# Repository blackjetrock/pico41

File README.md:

This project has been superseded by Tulip
=========================================

It is recommeded that the Tulip project is used instead of this one. It can be found here:

https://github.com/mjakuipers/TULIP-DevBoard

It has more features, by far. The only feature that it doesn't have is the key pressing, but it does have many more ways to enter programs...

Pico41
======

This is a PCB that can be attached to an HP41C (using wires soldered to the processor PCB of the HP41C) that allows:

* The HP41C bus to be examined and traced
* Data to be placed on the bus
* Keys on the keyboard to be pressed
* viewing of the display on an OLED display on the PCB

You can see what is happening on the bus just like a logic analyser. The tracing (and other interaction) is through the USB of the Pico.
You can emulate modules by putting appropriate words on the bus. Currently I have emulated a MATH module. Bank switched modules aren't supported, nor are RAM modules, but that is just a matter of code that I haven't done yet.
You can press keys on the keyboard, so can enter programs by pressing the appropriate keys. I have a script that converts program in text form and embeds the keypresses into the Pico program such that they can be played back in PRGM mode. Once entered like this the program can be SST'd automatically and checked against a listing that is also embedded in the Pio program.

RP Pico on HP41C bus, showing an emulated MATH module where one word has been altered:

To Do
=====

It should be possible to emulate the display controller and use this Pico setup as a replacement for the display controller. For example a broken display controller should be replaceable by this program.
RAM should also be emulatable with more code.
Module code could be changed over USB rather than being embedded in the Pico code as it is now.

More Information
================

* https://youtu.be/KFQwrbWywjY
* https://youtu.be/kRxo2ekzvyg

This is a work in progress
==========================

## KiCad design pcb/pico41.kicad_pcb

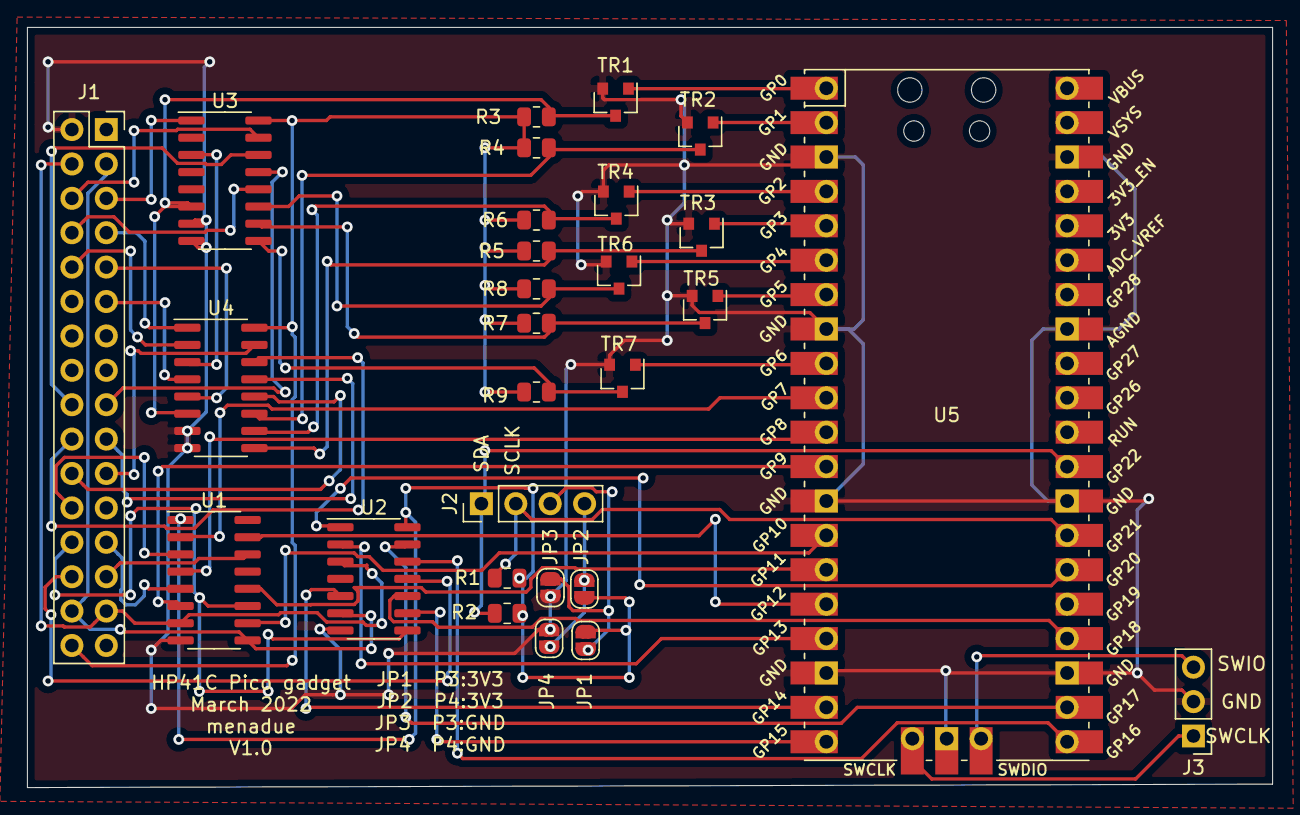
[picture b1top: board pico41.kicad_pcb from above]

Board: 2 copper layers, 91.9 x 56.1 mm, 28 parts (0 on the bottom side), 57 nets.

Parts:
J1: Conn_02x16_Counter_Clockwise; PinSocket_2x16_P2.54mm_Vertical
J2: Conn_01x04_Female; PinHeader_1x04_P2.54mm_Vertical
J3: Conn_01x03_Female; PinHeader_1x03_P2.54mm_Vertical
JP1, JP2, JP3, JP4: Jumper_NO_Small; SolderJumper-2_P1.3mm_Open_RoundedPad1.0x1.5mm
R1, R2: 4k7; R_0805_2012Metric
R3, R4, R5, R6, R7, R8, R9: 10k; R_0805_2012Metric
TR1: Si2302; SOT-23
TR2, TR3, TR4, TR5, TR6, TR7: si2302; SOT-23
U1: 4050; SOIC-16_3.9x9.9mm_P1.27mm
U2: 74LS125; SOIC-14_3.9x8.7mm_P1.27mm
U3, U4: 4051; SOIC-16_3.9x9.9mm_P1.27mm
U5: Pico; RPi_Pico_SMD_TH

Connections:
3V3: JP1.1, JP2.1, R1.1, R2.1, U1.1, U2.14
DATA: J1.4, J1.29, U1.7, U2.3
FI: J1.28, U2.11
GND: J1.2, J3.2, JP3.1, JP4.1, TR1.2, TR2.2, TR3.2, TR4.2, TR5.2, TR6.2, TR7.2, U1.8, U2.7, U3.7, U3.8, U4.7, U4.8, U5.3, U5.8, U5.13, U5.18, U5.23, U5.28, U5.33, U5.38, U5.42
I2C_SCL: J2.2, R1.2, U5.27
I2C_SDA: J2.1, R2.2, U5.29
ISA: J1.3, J1.30, U1.9, U2.6
KB_INH: R3.2, TR1.3, U3.6, U4.6
KC0: J1.17, U3.13
KC1: J1.18, U3.14
KC2: J1.6, U3.15
KC3: J1.8, U3.12
KC4: J1.5, U3.1
KCA: R8.2, TR6.3, U3.11
KCB: R7.2, TR5.3, U3.10
KCC: R9.2, TR7.3, U3.9
KR0: J1.19, U4.13
KR1: J1.20, U4.14
KR2: J1.21, U4.15
KR3: J1.22, U4.12
KR4: J1.7, U4.1
KR5: J1.9, U4.5
KR6: J1.10, U4.2
KR7: J1.11, U4.4
KRA: R4.2, TR2.3, U4.11
KRB: R6.2, TR4.3, U4.10
KRC: R5.2, TR3.3, U4.9
unnamed: J2.3, JP1.2, JP3.2
unnamed: J2.4, JP2.2, JP4.2
unnamed: U3.3, U4.3
PHI1: J1.24, U1.3
PHI2: J1.25, U1.5
PWO: J1.27, U1.14
P_DATA: U1.6, U5.12
P_DATA_DRV: U2.2, U5.17
P_DATA_OE: U2.1, U5.26
P_FI_DRV: U2.12, U5.21
P_FI_OE: U2.13, U5.22
P_ISA: U1.10, U5.14
P_ISA_DRV: U2.5, U5.19
P_KB_INH: TR1.1, U5.1
P_KCA: TR6.1, U5.6
P_KCB: TR5.1, U5.7
P_KCC: TR7.1, U5.9
P_KRA: TR2.1, U5.2
P_KRB: TR4.1, U5.4
P_KRC: TR3.1, U5.5
P_PHI1: U1.2, U5.10
P_PHI2: U1.4, U5.11
P_PWO: U1.15, U5.16
P_SYNC: U1.12, U5.15
P_SYNC_DRV: U2.9, U5.20
P_SYNC_OE: U2.10, U5.24
SWCLK: J3.1, U5.41
SWIO: J3.3, U5.43
SYNC: J1.26, U1.11, U2.8
VCC: J1.32, R3.1, R4.1, R5.1, R6.1, R7.1, R8.1, R9.1, U3.16, U4.16

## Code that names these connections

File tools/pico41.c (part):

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// GPIO Pins
//

const uint P_KB_INH            = 0;
const uint P_KRA               = 1;
const uint P_KRB               = 2;
const uint P_KRC               = 3;

const uint P_KCA               = 4;
const uint P_KCB               = 5;
const uint P_KCC               = 6;

const uint P_CLK1              = 7;
const uint P_CLK2              = 8;

const uint P_DATA              = 9;
const uint P_ISA               = 10;
const uint P_SYNC              = 11;
const uint P_PWO               = 12;
const uint P_DATA_DRV          = 13;
const uint P_ISA_DRV           = 14;
const uint P_SYNC_DRV          = 15;
const uint P_FI_DRV            = 16;
const uint P_FI_OE             = 17;
const uint P_SYNC_OE           = 18;
const uint P_ISA_OE            = 19;
const uint P_DATA_OE           = 20;

// For the OLED display
const uint SDA_PIN             = 22;
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  while(1)
    {
      // All switches off
      gpio_put(P_KB_INH, 0);
      sleep_us(1);
      gpio_put(P_KB_INH, 1);
      sleep_us(1);
    }
#endif
        gpio_put(P_KB_INH, 1);
}


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
void kb_init()
{
  gpio_init(P_KB_INH);
  gpio_init(P_KRA);
  gpio_init(P_KRB);
  gpio_init(P_KRC);
  gpio_init(P_KCA);
  gpio_init(P_KCB);
  gpio_init(P_KCC);

#if 1
  gpio_set_dir(P_KB_INH, GPIO_OUT);
  gpio_set_dir(P_KRA, GPIO_OUT);
  gpio_set_dir(P_KRB, GPIO_OUT);
  gpio_set_dir(P_KRC, GPIO_OUT);
  gpio_set_dir(P_KCA, GPIO_OUT);
  gpio_set_dir(P_KCB, GPIO_OUT);
  gpio_set_dir(P_KCC, GPIO_OUT);
#endif
  
  kb_all_off();
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
void drv_init(void)
{
  const uint P_FI_OE             = 17;
const uint P_SYNC_OE           = 18;
const uint P_ISA_OE            = 19;
const uint P_DATA_OE           = 20;

  gpio_init(P_FI_OE);
  gpio_init(P_SYNC_OE);
  gpio_init(P_ISA_OE);
  gpio_init(P_DATA_OE);

  gpio_set_dir(P_FI_OE, GPIO_OUT);
  gpio_set_dir(P_SYNC_OE, GPIO_OUT);
  gpio_set_dir(P_ISA_OE, GPIO_OUT);
  gpio_set_dir(P_DATA_OE, GPIO_OUT);

  gpio_put(P_FI_OE, 1);
  gpio_put(P_SYNC_OE, 1);
  gpio_put(P_ISA_OE, 1);
  gpio_put(P_DATA_OE, 1);

  gpio_init(P_ISA_DRV);
  gpio_set_dir(P_ISA_DRV, GPIO_OUT);
  gpio_put(P_ISA_DRV, 0);
}

////////////////////////////////////////////////////////////////////////////////
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  gpio_set_dir(P_CLK1, GPIO_IN);
  gpio_init(P_CLK2);
  gpio_set_dir(P_CLK2, GPIO_IN);
  gpio_init(P_SYNC);
  gpio_set_dir(P_SYNC, GPIO_IN);
  gpio_init(P_ISA);
  gpio_set_dir(P_ISA, GPIO_IN);
  gpio_init(P_DATA);
  gpio_set_dir(P_DATA, GPIO_IN);
  
}

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  
  // Wait for falling edge of sync, that is the start of a cycle
  
  last_sync = gpio_get(P_SYNC);
  
  while(1)
    {
      sync = gpio_get(P_SYNC);
      if( (last_sync==1) && (sync==0) )
	{
	  // Start of cycle
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    {
      fclk1[i] = gpio_get(P_CLK1);
      fclk2[i] = gpio_get(P_CLK2);
      fsync[i] = gpio_get(P_SYNC);
      fisa[i] =  gpio_get(P_ISA);
      fdata[i] = gpio_get(P_DATA);
    }
  
  // Display on USB
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
  irq_set_mask_enabled(0xffffffff, false);
    
  last_sync = gpio_get(P_SYNC);
  last_clk1 = gpio_get(P_CLK1);
  
  for(int i=0; i<NUM_FRAG; i++)
    {
      fclk1[i] = gpio_get(P_CLK1);
      fclk2[i] = gpio_get(P_CLK2);
      fsync[i] = gpio_get(P_SYNC);
      fisa[i] =  gpio_get(P_ISA);
      fdata[i] = gpio_get(P_DATA);


      // If clk1 has a low edge then count it
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  int last_sync;
  int last_clk1;

  last_sync = gpio_get(P_SYNC);
  last_clk1 = gpio_get(P_CLK1);
  
  for(int i=0; i<NUM_FRAG; i++)
    {
      fclk1[i] = gpio_get(P_CLK1);
      fclk2[i] = gpio_get(P_CLK2);
      fsync[i] = gpio_get(P_SYNC);
      fisa[i] =  gpio_get(P_ISA);
      fdata[i] = gpio_get(P_DATA);


      // If clk1 has a low edge then count it
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  
  clk1 = gpio_get(P_CLK1);
  clk2 = gpio_get(P_CLK2);
  sync = gpio_get(P_SYNC);
  isa =  gpio_get(P_ISA);
  data = gpio_get(P_DATA);

  printf("\nclk1=%d clk2=%d sync=%d isa=%d data=%d\n", clk1, clk2, sync, isa, data);
}
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  int instruction = 0;
  int bit_no      = 0;
  int gpio_states = 0;
  int sync        = 0;
  int address     = 0;
  int  data56      = 0;
  
  gpio_states = sio_hw->gpio_in;
  last_sync = gpio_states & (1<<P_SYNC);  

  while(1)
    {
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	}

      // Another bit, check SYNC to find bit number
      sync = gpio_states & (1<<P_SYNC);

      if( (last_sync == 0) && (sync != 0) )
	{
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      // Get data and put into data or instruction if bit no is OK for those fields
      if( (bit_no >= 44) && (bit_no <= 53) )
	{
	  instruction |= ((gpio_states & (1<<P_ISA))>>(P_ISA)) << ((bit_no - 44));
#if TDB	  
	  printf("\nI=%d (%08X)", instruction, gpio_states & (1<<P_ISA));
#endif

	}
      
      if( (bit_no >= 14) && (bit_no <= 29) )
	{
	  address |= ((gpio_states & (1<<P_ISA))>>(P_ISA)) << ((bit_no - 14));
#if TDB
	  printf("\nA=%d (%08X)", address, gpio_states & (1<<P_ISA));
#endif

	}

      if( (bit_no >= 0) && (bit_no <= 7) )
	{
	  periph_addr |= ((gpio_states & (1<<P_DATA))>>(P_DATA)) << ((bit_no - 0));
	}

      if( (bit_no >= 0) && (bit_no <= 55) )
	{
	  data56 |= ((gpio_states & (1<<P_DATA))>>(P_DATA)) << ((bit_no - 0));
	}
      
      // If bitno = 55 then we have another frame, store the transaction
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  row ^=0x7;
  if( row & 1 )
    {
      gpio_put(P_KRA, 1);
    }
  else
    {
      gpio_put(P_KRA, 0);
    }
  
  if( row & 2 )
    {
      gpio_put(P_KRB, 1);
    }
  else
    {
      gpio_put(P_KRB, 0);
    }
  
  if( row & 4 )
    {
      gpio_put(P_KRC, 1);
    }
  else
    {
      gpio_put(P_KRC, 0);
    }
}

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  col ^=0x7;
  if( col & 1 )
    {
      gpio_put(P_KCA, 1);
    }
  else
    {
      gpio_put(P_KCA, 0);
    }
  
  if( col & 2 )
    {
      gpio_put(P_KCB, 1);
    }
  else
    {
      gpio_put(P_KCB, 0);
    }
  
  if( col & 4 )
    {
      gpio_put(P_KCC, 1);
    }
  else
    {
      gpio_put(P_KCC, 0);
    }
}

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
void press_key(char *key)
{
  gpio_put(P_KB_INH, 0);
  sleep_ms(50);

  int i=0;
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	  setcol(key_def[i].key_c);
	  
	  // Press the key
	  gpio_put(P_KB_INH, 1);
	  sleep_ms(50);
	  gpio_put(P_KB_INH, 0);
	  
	  break;
	}
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
void kb_inhibit(void)
{
  gpio_put(P_KB_INH, 1);
}

void kb_uninhibit(void)
{
  gpio_put(P_KB_INH, 0);
}

void kb_active(void)
{
  gpio_put(P_KCA, 1);
  gpio_put(P_KCB, 1);
  gpio_put(P_KCC, 1);
  gpio_put(P_KCA, 1);
  gpio_put(P_KCB, 1);
  gpio_put(P_KCC, 1);
}

////////////////////////////////////////////////////////////////////////////////
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
int clk1 = 0;
int clk2 = 0;
int isa  = 0;

#define RISING_EDGE(SIGNAL)  ((last_ ## SIGNAL==0) && (SIGNAL==1))
#define FALLING_EDGE(SIGNAL) ((last_ ## SIGNAL==1) && (SIGNAL==0))
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int instruction = 0;
int bit_no      = 0;
int gpio_states = 0;
int sync        = 0;
int address     = 0;
uint64_t data56      = 0;

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  irq_set_mask_enabled(0xffffffff, false);
    
  gpio_states = sio_hw->gpio_in;
  last_sync = gpio_states & (1<<P_SYNC);  

  while(1)
    {
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	}

      // Another bit, check SYNC to find bit number
      sync = gpio_states & (1<<P_SYNC);

      // Do we drive the ISA line?
      // Bit numbers are out by one as bit_no hasn't been incremented yet.
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	    {
	      // Drive the ISA line for this data bit
	      gpio_put(P_ISA_OE, 0);
	      gpio_put(P_ISA_DRV, (drive_data & 1));
	      drive_data >>= 1;
	      driven_isa++;
	    }
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	}

      // Another bit, check SYNC to find bit number
      sync = gpio_states & (1<<P_SYNC);


      if( (last_sync == 0) && (sync != 0) )
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      
      if( (bit_no >= 44) && (bit_no <= 53) )
	{
	  instruction |= ((gpio_states & (1<<P_ISA))>>(P_ISA)) << ((bit_no - 44));
	}

      
      if( (bit_no >= 14) && (bit_no <= 29) )
	{
	  address |= ((gpio_states & (1<<P_ISA))>>(P_ISA)) << ((bit_no - 14));
	}
      
      // Got address. If the address is that of the embedded ROM then we flag that we have
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      
      if( (bit_no >= 0) && (bit_no <= 7) )
	{
	  periph_addr |= ((gpio_states & (1<<P_DATA))>>(P_DATA)) << ((bit_no - 0));
	}

      if( (bit_no >= 0) && (bit_no <= 55) )
	{
	  uint64_t v;
	  v = ((gpio_states & (1<<P_DATA))>>(P_DATA));
	  v <<= ((bit_no - 0));
	  data56 |= v;
	}
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  
  last_clk1 = gpio_get(P_CLK1);
  last_clk2 = gpio_get(P_CLK2);
  last_isa  = gpio_get(P_ISA);
  last_sync = gpio_get(P_SYNC);
  last_data = gpio_get(P_DATA);
  
  while(1)
    {
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      gpios = sio_hw->gpio_in;
      clk1 = (gpios >> P_CLK1) & 1;
      clk2 = (gpios >> P_CLK2) & 1;
      sync = (gpios >> P_SYNC) & 1;
      isa  = (gpios >> P_ISA) & 1;
      data = (gpios >> P_DATA) & 1;
#else
      clk1 = gpio_get(P_CLK1);
      clk2 = gpio_get(P_CLK2);
      isa  = gpio_get(P_ISA);
      sync = gpio_get(P_SYNC);
      data = gpio_get(P_DATA);
#endif

      // Wait for clk2 edge
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	}
      
      //      buffer[buffer_i] = gpio_get(P_CLK1);
      buffer[buffer_i++] = gpios2 & ((1 << P_CLK1) |(1 << P_CLK2) | (1<<P_SYNC) | (1<<P_DATA)| (1<<P_ISA));
      
      isa  = gpios2 & (1<<P_ISA);
      data = gpios2 & (1<<P_DATA);
      sync = gpios2 & (1<<P_SYNC);
      
      if( (last_sync!=0) && (sync==0) )
	{
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
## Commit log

2023-06-01 Fixed R/S keystroke. Byte grabber sequence now works at least as far as it gets
2023-06-02 Added comment
